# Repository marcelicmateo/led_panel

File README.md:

# LED pannel 
RGB led panel driver on esp8266, nodemcuv1

## KICAD 
project containing PCB documentation is under hardware folder

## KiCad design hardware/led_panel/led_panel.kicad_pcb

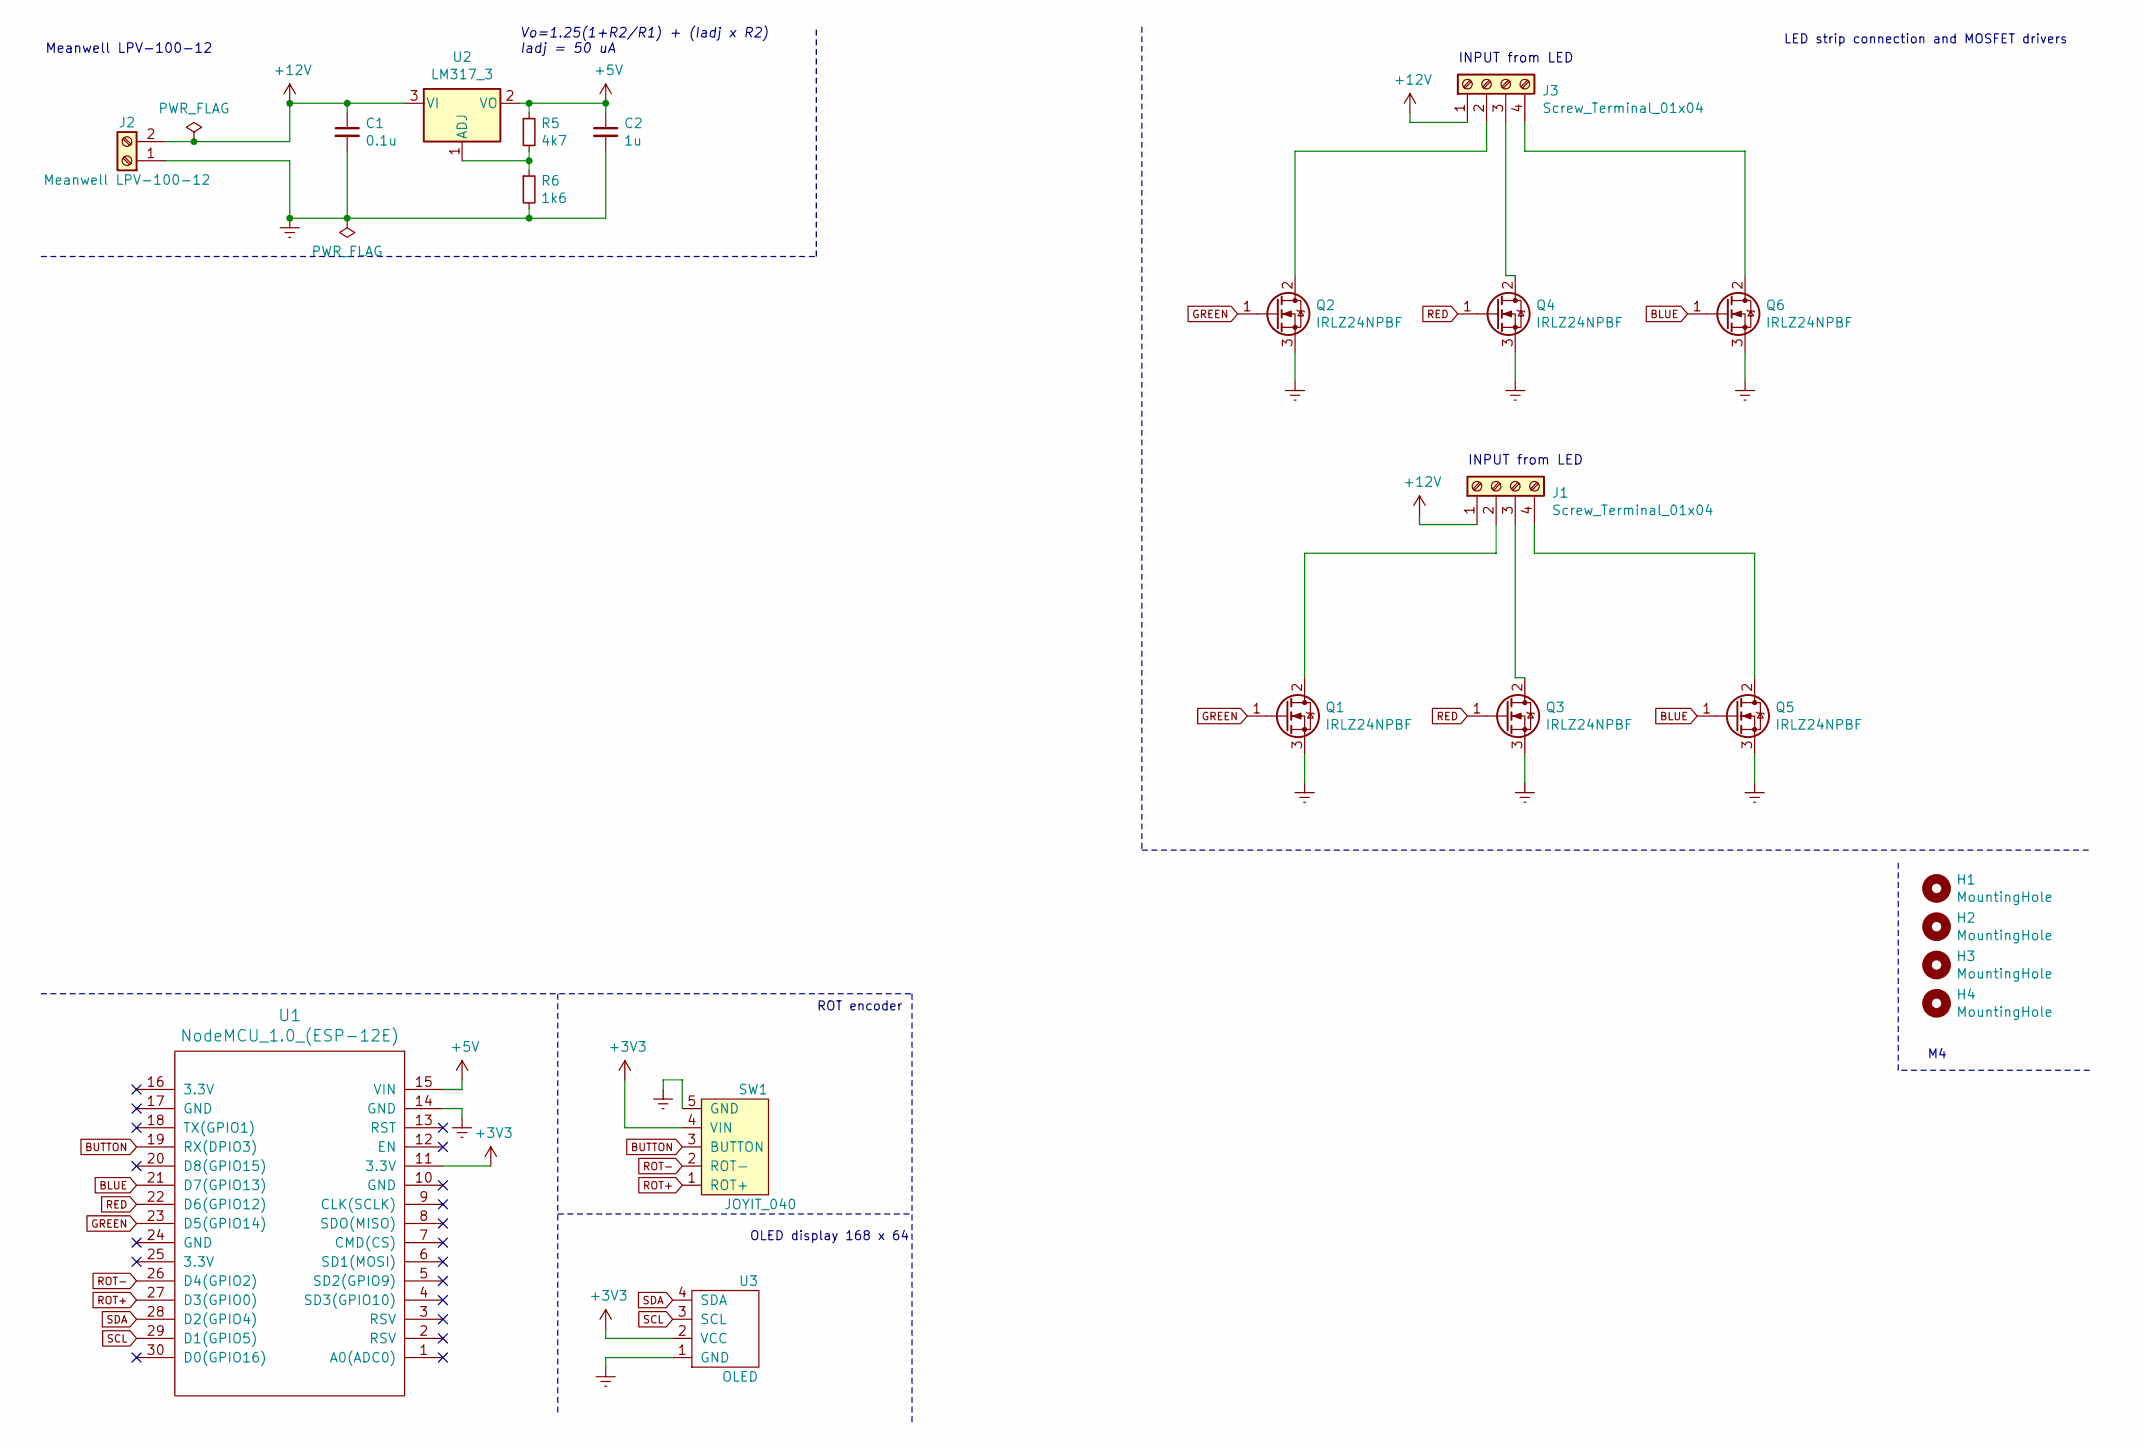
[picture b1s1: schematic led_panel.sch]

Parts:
C1: 0.1u; C_Radial_D5.0mm_H7.0mm_P2.00mm
C2: 1u; C_Radial_D5.0mm_H7.0mm_P2.00mm
H1, H2, H3, H4: MountingHole; MountingHole_4.3mm_M4_DIN965
J1, J3: Screw_Terminal_01x04; TerminalBlock_Phoenix_MKDS-1,5-4_1x04_P5.00mm_Horizontal
J2: Meanwell LPV-100-12; TerminalBlock_Phoenix_MKDS-1,5-2_1x02_P5.00mm_Horizontal
Q1, Q2, Q3, Q4, Q5, Q6: IRLZ24NPBF; TO-220-3_Vertical
R5: 4k7; R_Axial_DIN0207_L6.3mm_D2.5mm_P7.62mm_Horizontal
R6: 1k6; R_Axial_DIN0207_L6.3mm_D2.5mm_P7.62mm_Horizontal
SW1: JOYIT_040; PinHeader_1x05_P2.54mm_Vertical
U1: NodeMCU_1.0_(ESP-12E); ESP12F-Devkit-V3
U2: LM317_3; TO-220-3_Vertical
U3: OLED; PinHeader_1x04_P2.54mm_Vertical

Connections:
+3V3: SW1.4 (VIN), U1.11 (3.3V), U3.2 (VCC)
+5V: C2.1, R5.1, U1.15 (VIN), U2.2 (VO)
+12V: C1.1, J1.1, J2.2, J3.1, U2.3 (VI)
BLUE: Q5.1 (G), Q6.1 (G), U1.21 (D7(GPIO13))
BUTTON: SW1.3 (BUTTON), U1.19 (RX(DPIO3))
Earth: C1.2, C2.2, J2.1, Q1.3 (S), Q2.3 (S), Q3.3 (S), Q4.3 (S), Q5.3 (S), Q6.3 (S), R6.2, SW1.5 (GND), U1.14 (GND), U3.1 (GND)
GREEN: Q1.1 (G), Q2.1 (G), U1.23 (D5(GPIO14))
unnamed: J1.2, Q1.2 (D)
unnamed: J1.3, Q3.2 (D)
unnamed: J1.4, Q5.2 (D)
unnamed: J3.2, Q2.2 (D)
unnamed: J3.3, Q4.2 (D)
unnamed: J3.4, Q6.2 (D)
unnamed: R5.2, R6.1, U2.1 (ADJ)
RED: Q3.1 (G), Q4.1 (G), U1.22 (D6(GPIO12))
ROT+: SW1.1 (ROT+), U1.27 (D3(GPIO0))
ROT-: SW1.2 (ROT-), U1.26 (D4(GPIO2))
SCL: U1.29 (D1(GPIO5)), U3.3 (SCL)
SDA: U1.28 (D2(GPIO4)), U3.4 (SDA)

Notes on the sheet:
Meanwell LPV-100-12
Vo=1.25(1+R2/R1) + (Iadj x R2) Iadj = 50 uA
INPUT from LED
OLED display 168 x 64
ROT encoder
LED strip connection and MOSFET drivers

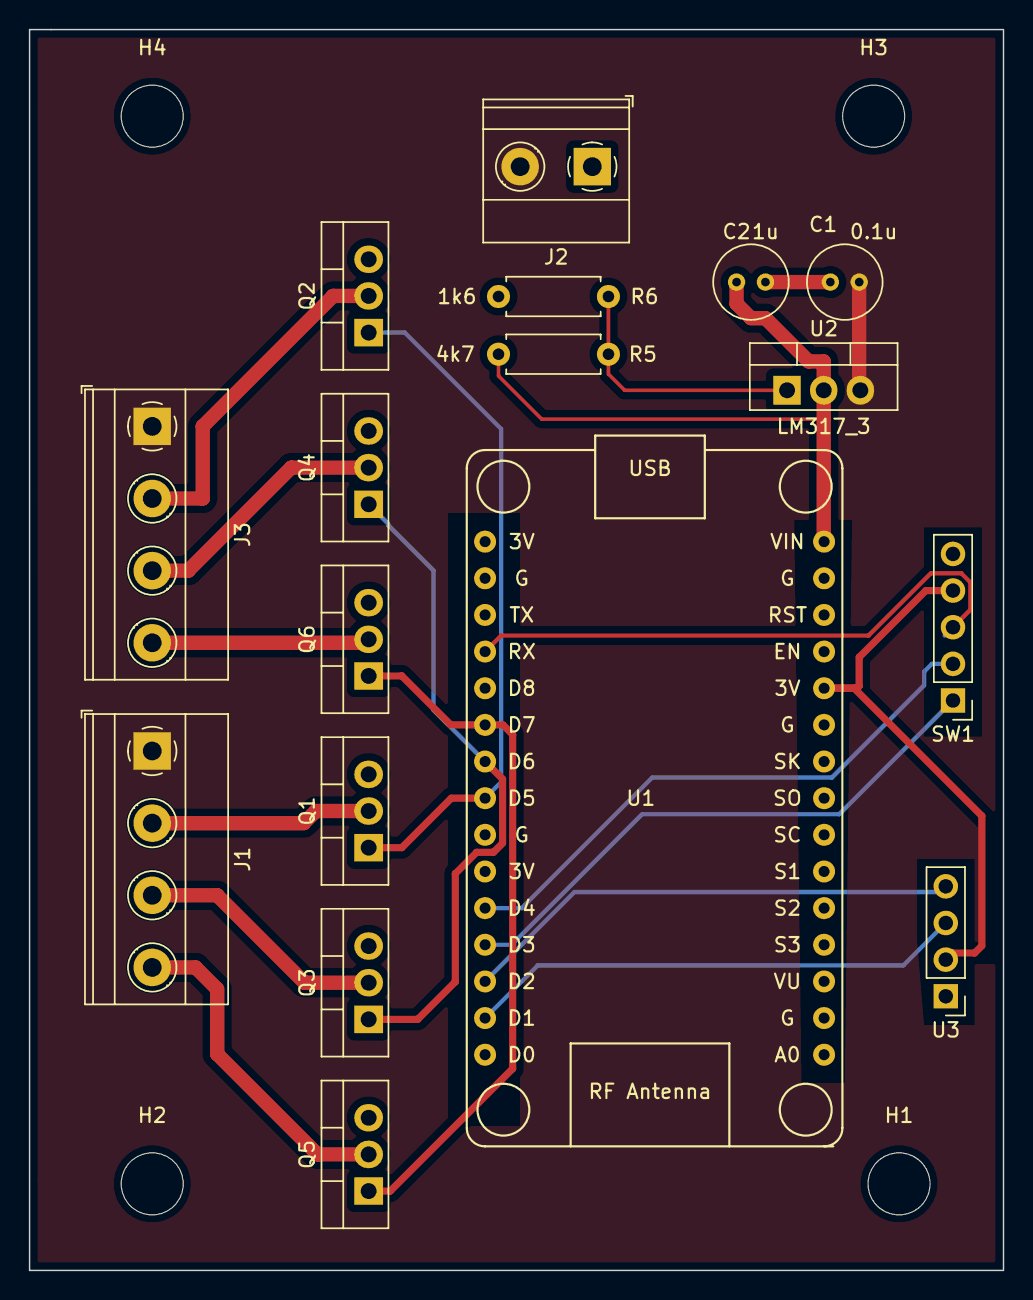
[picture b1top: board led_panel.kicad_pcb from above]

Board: 2 copper layers, 67.5 x 86.0 mm, 21 parts (0 on the bottom side), 19 nets.

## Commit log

2020-09-26 fixed reboot isue
2020-10-28 1 version of pcb
2020-11-09 minor fix
2020-11-09 update git ignore
2020-11-11 add structures
2020-11-11 cleen up
2020-11-11 code cleanup
2020-11-11 documenting functions
2020-11-11 only necessary kicad files
2020-11-11 flag optimization
2020-12-17 anlog led library
2021-04-13 fix dewpendencies
2021-04-13 git ignore for kicad
2021-04-23 kicad tidy
